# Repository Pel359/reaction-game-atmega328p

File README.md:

# Игра на реакцию для двух игроков на ATmega328P

DIY-гаджет: игра на реакцию для двух игроков. После случайной задержки загорается центральный зелёный светодиод — кто быстрее нажмёт свою кнопку, тот выигрывает раунд. Первый до 3 очков выигрывает матч.

Проект на "голом" ATmega328P (без Arduino-платы). Код написан в Arduino IDE (только core-функции, без библиотек), прошивка HEX-файлом через программатор (T48).

## Оглавление
- [Версии](#версии)
- [Механика игры](#механика-игры)
- [Список компонентов (BOM)](#список-компонентов-bom)
- [Сборка и прошивка](#сборка-и-прошивка)
- [Код](#код)

## Версии
- **v1.0** : простая индикация — LED1 (P1) и  LED2 (P2) мигают при победе в раунде. При победе в матче — быстрое мигание индикатора победителя.
  
- **v2.0** (в разработке): улучшенная индикация — по три LED на игрока . Индикаторы счёта зажигаются последовательно и остаются гореть. При победе в матче — красивая поочерёдная анимация всех трёх индикаторов победителя.

## Механика игры (общая для обеих версий)
- Стартовый сигнал: 3 коротких моргания центрального  LED.
- Случайная задержка 1–5 секунд.
- Анти-чит: более 2 нажатий кнопки во время ожидания — игрок блокируется на раунд.
- После загорания центрального LED — 5 секунд на реакцию.
- Матч до 3 очков.
- Автоматический сброс после окончания матча.

## Список компонентов (BOM)

| Компонент                  | Кол-во (v1.0) | Кол-во (v2.0) | Примечание                  |
|----------------------------|---------------|---------------|-----------------------------|
| ATmega328P                 | 1             | 1             |                             |
| Тактовые кнопки 6×6 мм     | 2             | 2             |                             |
| Светодиод   smd (0805)     | 1             | 1             | Центральный                 |
| Светодиод smd (0805)       | 1             | 3             | P1                          |
| Светодиод smd (0805)       | 1             | 3             | P2                          |
| Резисторы                  | 3             | 7             | Для LED        330 Ом       |
| Резисторы                  | 1             | 1             |                10 кОм       |
| Батарейный отсек CR2032    | 1             | 1             |                             |
| Конденсатор                | 1             | 1             | 1мКф                        | 

## Код

- v1.0: `/src/v1/reaction_game_v1.ino`
- v2.0: `/src/v2/reaction_game_v2.ino`
- HEX-файлы: `/firmware/`

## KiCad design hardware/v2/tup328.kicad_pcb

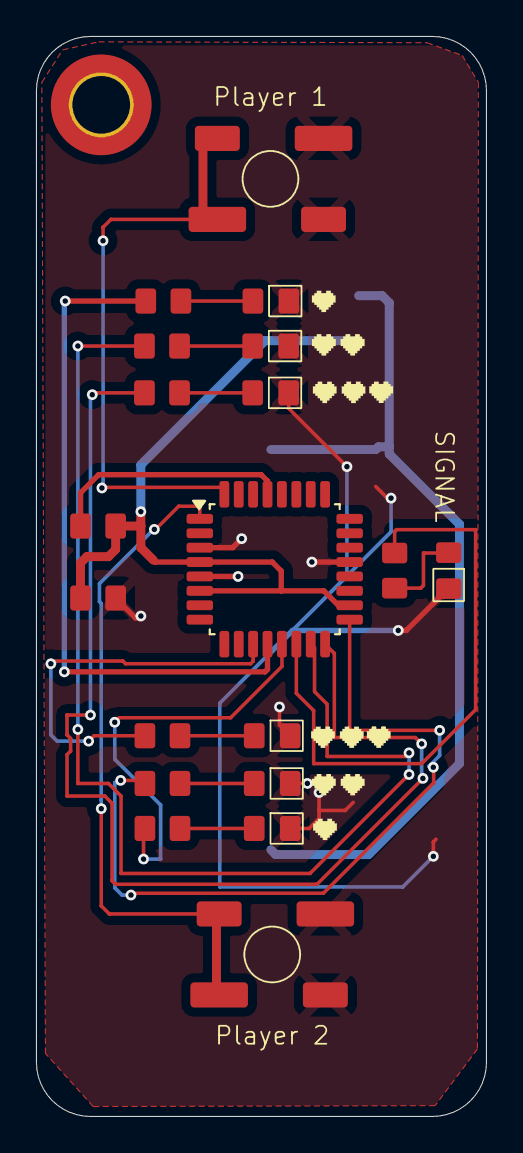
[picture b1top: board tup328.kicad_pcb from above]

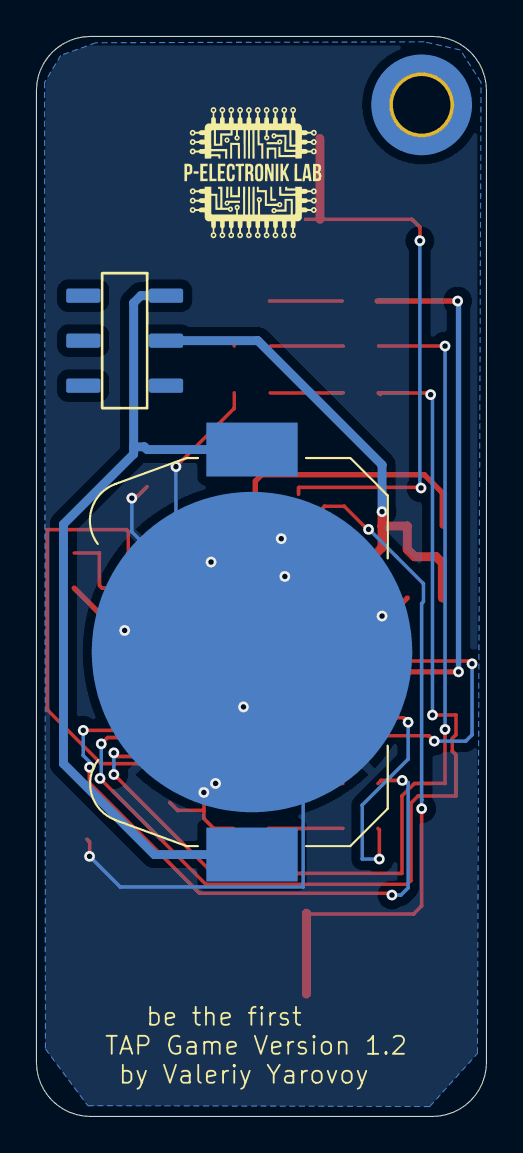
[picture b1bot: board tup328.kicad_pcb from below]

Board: 2 copper layers, 25.0 x 60.0 mm, 22 parts (2 on the bottom side), 20 nets.

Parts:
BT1: Battery_Cell; tupBatteryHolder_Keystone_3034_1x20mm
C1: 1uF; 0805_Capacitor_prodject_version1_copy
D1, D2, D4, D5, D6, D7: 0805_LED_prodject_version1
H1: MountingHole; MountingHole_3.2mm_M3_DIN965_Pad_TopBottom
Player 1 , Player 2: SW_MEC_5E; SWITCH_6x6_Led_peoject
R1, R2, R3, R4, R5, R6, R7, R8: R; 0805_Capacitor_prodject_version1_copy
SIGNAL: 0805_LED_prodject_version1
SW3: SW_DPDT_x2; Knopka 1
U1: ATmega328P-A; TQFP-32_7x7mm_P0.8mm

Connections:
GND: BT1.2 (-), C1.2, D1.2 (K), D2.2 (K), D4.2 (K), D5.2 (K), D6.2 (K), D7.2 (K), Player 1.3 (K), Player 1.4 (A), Player 2.3 (K), Player 2.4 (A), SIGNAL.2 (K), U1.3 (GND), U1.5 (GND), U1.21 (GND)
unnamed: BT1.1 (+), SW3.1 (A)
unnamed: D1.1 (A), R1.2
unnamed: D2.1 (A), R2.2
unnamed: R3.2, SIGNAL.1 (A)
unnamed: D4.1 (A), R5.2
unnamed: D5.1 (A), R6.2
unnamed: D6.1 (A), R7.2
unnamed: D7.1 (A), R8.2
unnamed: R1.1, U1.12 (PB0)
unnamed: R2.1, U1.13 (PB1)
unnamed: R3.1, U1.14 (PB2)
unnamed: R5.1, U1.15 (PB3)
unnamed: R6.1, U1.16 (PB4)
unnamed: R7.1, U1.17 (PB5)
unnamed: Player 1.1, Player 1.2, U1.32 (PD2)
unnamed: Player 2.1, Player 2.2, U1.1 (PD3)
unnamed: R8.1, U1.11 (PD7)
unnamed: R4.1, U1.29 (~RESET/PC6)
VCC: C1.1, R4.2, SW3.2 (B), U1.4 (VCC), U1.6 (VCC), U1.18 (AVCC)

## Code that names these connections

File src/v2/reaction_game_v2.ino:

#include <Arduino.h>

#define LED1_1 8   // Первый индикатор  P1 (PB0)
#define LED1_2 11  // Второй индикатор  P1 (PB3)
#define LED1_3 12  // Третий индикатор  P1 (PB4)
#define LED2   10  // Центр (PB2)
#define LED2_1 9   // Первый индикатор  P2 (PB1)
#define LED2_2 13  // Второй индикатор  P2 (PB5)
#define LED2_3 7   // Третий индикатор  P2 (PD7)
#define BUTTON1 2  // Кнопка P1
#define BUTTON2 3  // Кнопка P2

int scoreP1 = 0;
int scoreP2 = 0;

// Обновляем индикаторы счёта
void updateScoreLEDsP1() {
  digitalWrite(LED1_1, scoreP1 >= 1 ? HIGH : LOW);
  digitalWrite(LED1_2, scoreP1 >= 2 ? HIGH : LOW);
  digitalWrite(LED1_3, scoreP1 >= 3 ? HIGH : LOW);
}

void updateScoreLEDsP2() {
  digitalWrite(LED2_1, scoreP2 >= 1 ? HIGH : LOW);
  digitalWrite(LED2_2, scoreP2 >= 2 ? HIGH : LOW);
  digitalWrite(LED2_3, scoreP2 >= 3 ? HIGH : LOW);
}

// Анимация победы в матче (поочерёдное мигание всех трёх индикаторов 5 раз)
void victoryAnimationP1() {
  for (int i = 0; i < 5; i++) {
    digitalWrite(LED1_1, HIGH); delay(200); digitalWrite(LED1_1, LOW);
    digitalWrite(LED1_2, HIGH); delay(200); digitalWrite(LED1_2, LOW);
    digitalWrite(LED1_3, HIGH); delay(200); digitalWrite(LED1_3, LOW);
  }
}

void victoryAnimationP2() {
  for (int i = 0; i < 5; i++) {
    digitalWrite(LED2_1, HIGH); delay(200); digitalWrite(LED2_1, LOW);
    digitalWrite(LED2_2, HIGH); delay(200); digitalWrite(LED2_2, LOW);
    digitalWrite(LED2_3, HIGH); delay(200); digitalWrite(LED2_3, LOW);
  }
}

void normalRound() {
  // Рандомная задержка перед стартом
  unsigned long waitDuration = random(1000, 5001);
  unsigned long waitStart = millis();

  int cheatCountP1 = 0;
  int cheatCountP2 = 0;
  bool blockedP1 = false;
  bool blockedP2 = false;

  byte prevStateB1 = HIGH;
  byte prevStateB2 = HIGH;

  // Фаза ожидания (анти-спам)
  while (millis() - waitStart < waitDuration) {
    byte currentB1 = digitalRead(BUTTON1);
    if (currentB1 == LOW && prevStateB1 == HIGH) {
      cheatCountP1++;
      if (cheatCountP1 > 2) blockedP1 = true;
      while (digitalRead(BUTTON1) == LOW);
      delay(20);
    }
    prevStateB1 = currentB1;

    byte currentB2 = digitalRead(BUTTON2);
    if (currentB2 == LOW && prevStateB2 == HIGH) {
      cheatCountP2++;
      if (cheatCountP2 > 2) blockedP2 = true;
      while (digitalRead(BUTTON2) == LOW);
      delay(20);
    }
    prevStateB2 = currentB2;
  }

  // Старт раунда — зажигаем центр
  digitalWrite(LED2, HIGH);

  unsigned long reactionStart = millis();
  bool pressed = false;

  // Фаза реакции
  while (millis() - reactionStart < 5000 && !pressed) {
    if (!blockedP1 && digitalRead(BUTTON1) == LOW) {
      scoreP1++;
      updateScoreLEDsP1();   // Зажигаем следующий индикатор (и он остаётся гореть)
      digitalWrite(LED2, LOW);
      pressed = true;
    } else if (!blockedP2 && digitalRead(BUTTON2) == LOW) {
      scoreP2++;
      updateScoreLEDsP2();   // Зажигаем следующий индикатор (и он остаётся гореть)
      digitalWrite(LED2, LOW);
      pressed = true;
    }
  }

  if (!pressed) {
    digitalWrite(LED2, LOW);  
  }
}

void setup() {
  pinMode(LED1_1, OUTPUT);
  pinMode(LED1_2, OUTPUT);
  pinMode(LED1_3, OUTPUT);
  pinMode(LED2, OUTPUT);
  pinMode(LED2_1, OUTPUT);
  pinMode(LED2_2, OUTPUT);
  pinMode(LED2_3, OUTPUT);
  pinMode(BUTTON1, INPUT_PULLUP);
  pinMode(BUTTON2, INPUT_PULLUP);

  randomSeed(analogRead(A0));

  // Стартовый сигнал: 3 моргания центра
  for (int i = 0; i < 3; i++) {
    digitalWrite(LED2, HIGH);
    delay(500);
    digitalWrite(LED2, LOW);
    delay(500);
  }

  // На старте счёт 0 — все индикаторы погашены
  updateScoreLEDsP1();
  updateScoreLEDsP2();
}

void loop() {
  // Перед каждым раундом обновляем индикаторы (чтобы они продолжали гореть)
  updateScoreLEDsP1();
  updateScoreLEDsP2();
  digitalWrite(LED2, LOW);  

  normalRound();
// Проверка победы в матче (до 3 очков)
  if (scoreP1 >= 3) {
    victoryAnimationP1();  // Анимация победы
    scoreP1 = 0;
    scoreP2 = 0;
    // Гасим все индикаторы для нового матча
    digitalWrite(LED1_1, LOW);
    digitalWrite(LED1_2, LOW);
    digitalWrite(LED1_3, LOW);
    digitalWrite(LED2_1, LOW);
    digitalWrite(LED2_2, LOW);
    digitalWrite(LED2_3, LOW);
    delay(2000);
  } else if (scoreP2 >= 3) {
    victoryAnimationP2();
    scoreP1 = 0;
    scoreP2 = 0;
    digitalWrite(LED1_1, LOW);
    digitalWrite(LED1_2, LOW);
    digitalWrite(LED1_3, LOW);
    digitalWrite(LED2_1, LOW);
    digitalWrite(LED2_2, LOW);
    digitalWrite(LED2_3, LOW);
    delay(2000);
  }

  delay(1000);  // Пауза перед следующим раундом
}

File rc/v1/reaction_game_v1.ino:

#include <Arduino.h>
 
#define LED1 8   // PB0 (pin 14) - LED (P1)
#define LED3 9   // PB1 (pin 15) - LED (P2)
#define LED2 10  // PB2 (pin 16) - LED (центр)
#define BUTTON1 2 // PD2 (pin 4, digital 2) - Кнопка P1
#define BUTTON2 3 // PD3 (pin 5, digital 3) - Кнопка P2
 
int scoreP1 = 0;
int scoreP2 = 0;
 
void blinkLED(int led, int times, int delayMs) {
  for (int i = 0; i < times; i++) {
    digitalWrite(led, HIGH);
    delay(delayMs);
    digitalWrite(led, LOW);
    delay(delayMs);
  }
}
 
void normalRound() {
  // Рандомная задержка 1-5 секунд
  unsigned long waitDuration = random(1000, 5001);
  unsigned long waitStart = millis();
 
  int cheatCountP1 = 0;
  int cheatCountP2 = 0;
  bool blockedP1 = false;
  bool blockedP2 = false;
 
  byte prevStateB1 = HIGH;
  byte prevStateB2 = HIGH;
 
  // Фаза ожидания: мониторим спам кнопок
  while (millis() - waitStart < waitDuration) {
    byte currentB1 = digitalRead(BUTTON1);
    if (currentB1 == LOW && prevStateB1 == HIGH) { 
      cheatCountP1++;
      if (cheatCountP1 > 2) blockedP1 = true;
      while (digitalRead(BUTTON1) == LOW);  
      delay(20); 
    }
    prevStateB1 = currentB1;
 
    byte currentB2 = digitalRead(BUTTON2);
    if (currentB2 == LOW && prevStateB2 == HIGH) {
      cheatCountP2++;
      if (cheatCountP2 > 2) blockedP2 = true;
      while (digitalRead(BUTTON2) == LOW);
      delay(20);
    }
    prevStateB2 = currentB2;
  }
 
  // Зажигаем центральный LED — старт!
  digitalWrite(LED2, HIGH);
 
  unsigned long reactionStart = millis();
  bool pressed = false;
 
  // Фаза реакции (5 секунд)
  while (millis() - reactionStart < 5000 && !pressed) {
    if (!blockedP1 && digitalRead(BUTTON1) == LOW) {
      scoreP1++;
      digitalWrite(LED2, LOW);
      digitalWrite(LED1, HIGH);
      delay(1000);
      digitalWrite(LED1, LOW);
      pressed = true;
    } else if (!blockedP2 && digitalRead(BUTTON2) == LOW) {
      scoreP2++;
      digitalWrite(LED2, LOW);
      digitalWrite(LED3, HIGH);  
      delay(1000);
      digitalWrite(LED3, LOW);
      pressed = true;
    }
  }
 
  if (!pressed) {
    digitalWrite(LED2, LOW);  // Таймаут
  }
}
 
void setup() {
  pinMode(LED1, OUTPUT);
  pinMode(LED2, OUTPUT);
  pinMode(LED3, OUTPUT);
  pinMode(BUTTON1, INPUT_PULLUP);
  pinMode(BUTTON2, INPUT_PULLUP);
 
  digitalWrite(LED1, LOW);
  digitalWrite(LED2, LOW);
  digitalWrite(LED3, LOW);
 
  randomSeed(analogRead(A0));  // Seed для рандома
 
  // Стартовый сигнал: моргание центра 3 раза 
  blinkLED(LED2, 3, 500);
}
 
void loop() {
  // Сброс всех LED перед раундом
  digitalWrite(LED1, LOW);
  digitalWrite(LED2, LOW);
  digitalWrite(LED3, LOW);
 
  normalRound();
 
  // Проверка победы (до 3 очков)
  if (scoreP1 >= 3) {
    blinkLED(LED1, 5, 100);  // Победа P1 — 5 быстрых миганий 
    scoreP1 = 0;
    scoreP2 = 0;
    delay(2000);  // Пауза перед новым матчем
  } else if (scoreP2 >= 3) {
    blinkLED(LED3, 5, 100);  // Победа P2 — 5 быстрых миганий 
    scoreP1 = 0;
    scoreP2 = 0;
    delay(2000);
  }
 
  // Пауза перед следующим раундом
  delay(1000);
}

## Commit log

2026-01-26 Update README with accurate game description and version differences
2026-01-26 Create src folder structure
2026-01-28 Add source code for v1.0
2026-01-28 Add source code for v2.0
2026-01-28 Add HEX firmware files for v1.0 and v2.0
2026-01-28 Add photos for assembled v1.0 board
2026-01-28 Add photos for assembled v2.0 board
2026-01-28 Rename 2026-01-28_20-11-17.png to schematic.png
2026-01-28 Rename 2026-01-28_20-20-10.png to PCB 1.png
2026-01-28 Rename 2026-01-28_20-17-54.png to 3D Model.png
2026-01-28 Rename 2026-01-28_20-17-12.png to PCB 2.png
2026-01-28 Rename 2026-01-28_21-53-27.png to Schematic.png
2026-01-28 Add KiCad project files for v1.0
2026-01-28 Add KiCad project files for v2.0
2026-01-28 Add Gerber files for v1.0 and v2.0 manufacturing
